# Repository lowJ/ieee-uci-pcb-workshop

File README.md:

# ieee@uci-pcb-workshop
 open the .pro file in kicad

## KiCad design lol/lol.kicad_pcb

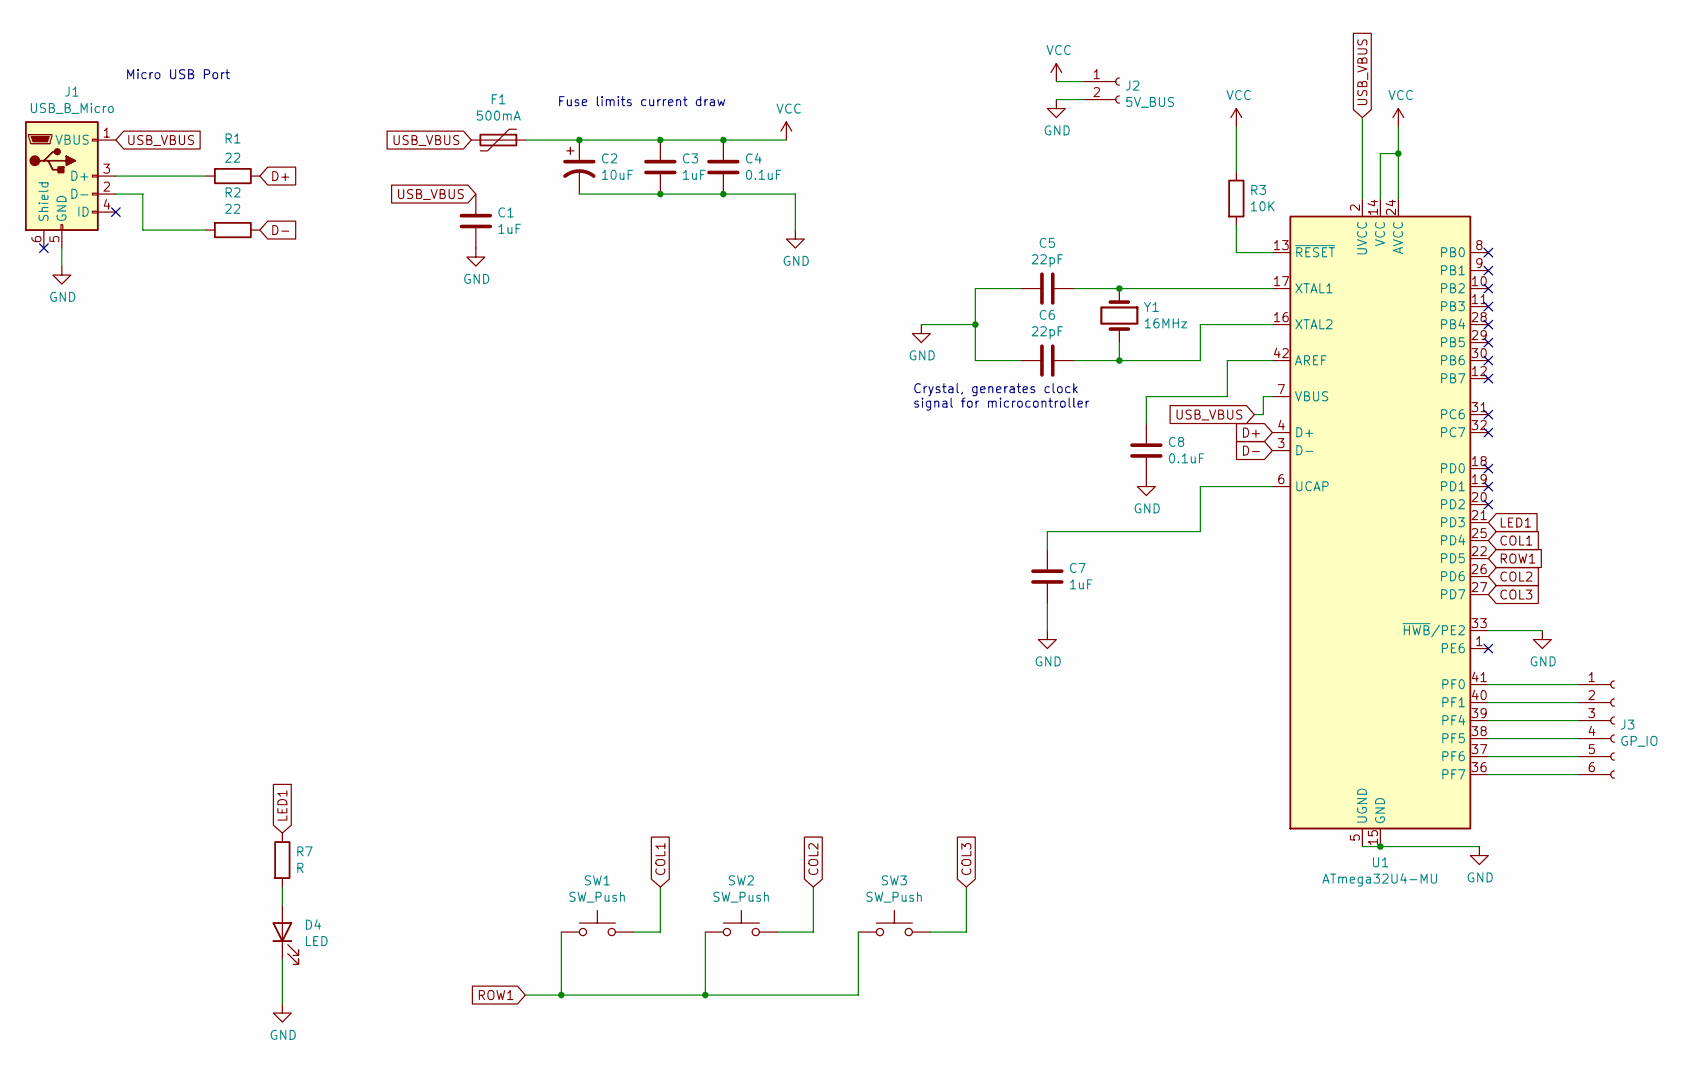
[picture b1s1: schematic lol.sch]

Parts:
C1, C3: 1uF; CP_Radial_D6.3mm_P2.50mm
C2: 10uF; CP_Radial_D6.3mm_P2.50mm
C4, C8: 0.1uF; C_1206_3216Metric_Pad1.33x1.80mm_HandSolder
C5, C6: 22pF; C_1206_3216Metric_Pad1.33x1.80mm_HandSolder
C7: 1uF; CP_Radial_D5.0mm_P2.00mm
D4: LED; LED_D4.0mm
F1: 500mA; Fuse_2010_5025Metric_Pad1.52x2.65mm_HandSolder
J1: USB_B_Micro; USB_Micro-AB_Molex_47590-0001
J2: 5V_BUS; PinSocket_1x02_P2.54mm_Vertical
J3: GP_IO; PinSocket_1x06_P2.54mm_Vertical
R1, R2: 22; R_1206_3216Metric_Pad1.30x1.75mm_HandSolder
R3: 10K; R_1206_3216Metric_Pad1.30x1.75mm_HandSolder
R7: R; R_Axial_DIN0204_L3.6mm_D1.6mm_P5.08mm_Horizontal
SW1, SW2, SW3: SW_Push; SW_PUSH_6mm
U1: ATmega32U4-MU; QFN-44-1EP_7x7mm_P0.5mm_EP5.2x5.2mm
Y1: 16MHz; Crystal_SMD_5032-2Pin_5.0x3.2mm_HandSoldering

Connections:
COL1: SW1.2, U1.25 (PD4)
COL2: SW2.2, U1.26 (PD6)
COL3: SW3.2, U1.27 (PD7)
D+: R1.1, U1.4 (D+)
D-: R2.1, U1.3 (D-)
GND: C1.2, C2.2, C3.2, C4.2, C5.1, C6.1, C7.2, C8.2, D4.1 (K), J1.5 (GND), J2.2, U1.5 (UGND), U1.15 (GND), U1.23 (GND), U1.33 (~HWB~/PE2), U1.35 (GND), U1.43 (GND), U1.45 (GND)
LED1: R7.1, U1.21 (PD3)
unnamed: C5.2, U1.17 (XTAL1), Y1.1
unnamed: C6.2, U1.16 (XTAL2), Y1.2
unnamed: C7.1, U1.6 (UCAP)
unnamed: C8.1, U1.42 (AREF)
unnamed: D4.2 (A), R7.2
unnamed: J1.2 (D-), R2.2
unnamed: J1.3 (D+), R1.2
unnamed: J3.1, U1.41 (PF0)
unnamed: J3.2, U1.40 (PF1)
unnamed: J3.3, U1.39 (PF4)
unnamed: J3.4, U1.38 (PF5)
unnamed: J3.5, U1.37 (PF6)
unnamed: J3.6, U1.36 (PF7)
unnamed: R3.2, U1.13 (~RESET)
ROW1: SW1.1, SW2.1, SW3.1, U1.22 (PD5)
USB_VBUS: C1.1, F1.2, J1.1 (VBUS), U1.2 (UVCC), U1.7 (VBUS)
VCC: C2.1, C3.1, C4.1, F1.1, J2.1, R3.1, U1.14 (VCC), U1.24 (AVCC), U1.34 (VCC), U1.44 (AVCC)

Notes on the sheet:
Crystal, generates clock signal for microcontroller
Fuse limits current draw
Micro USB Port

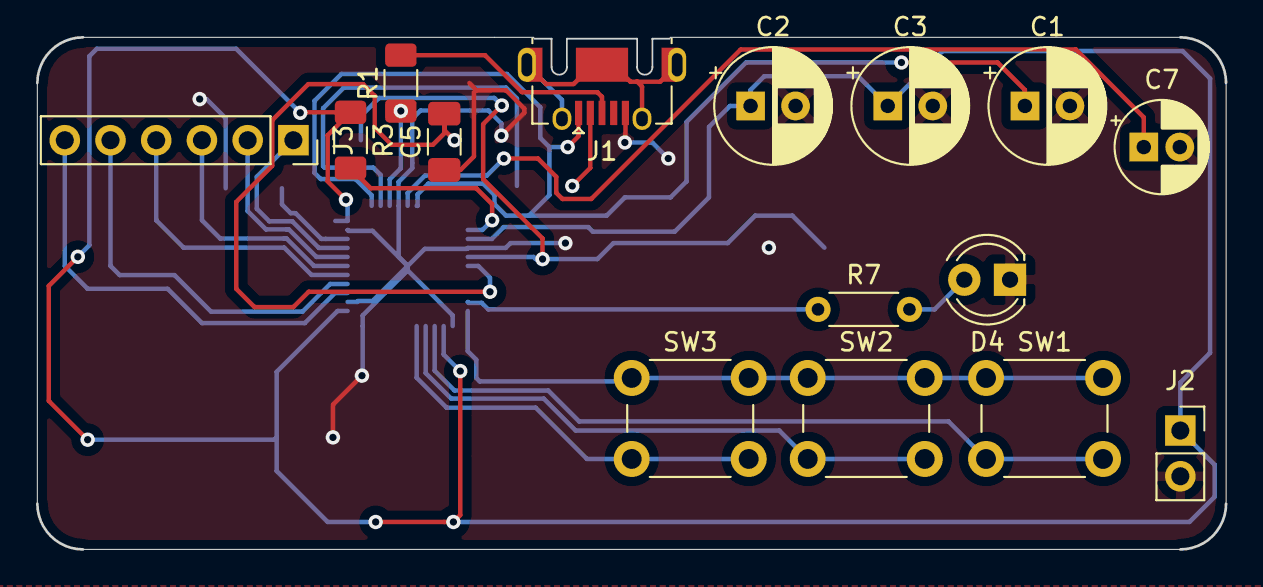
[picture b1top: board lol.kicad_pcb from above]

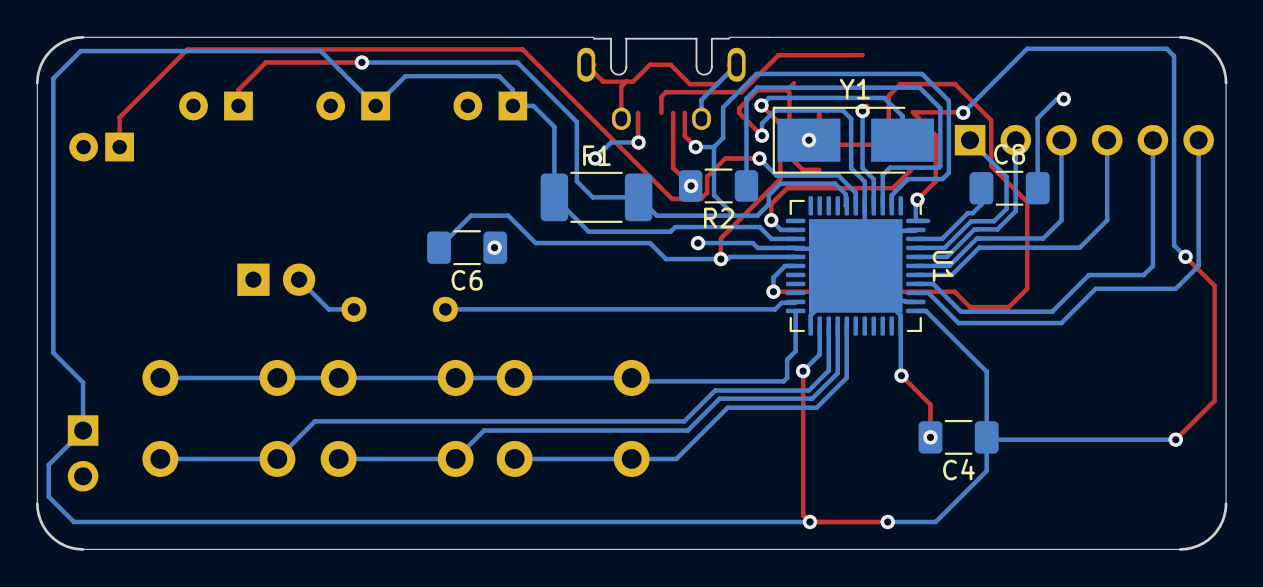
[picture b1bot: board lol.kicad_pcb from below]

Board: 2 copper layers, 66.0 x 28.4 mm, 22 parts (7 on the bottom side), 24 nets.

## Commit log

2020-10-26 finished schem and footprint matching
2020-10-26 didnt save files
2020-10-29 finished pcb... tired....
